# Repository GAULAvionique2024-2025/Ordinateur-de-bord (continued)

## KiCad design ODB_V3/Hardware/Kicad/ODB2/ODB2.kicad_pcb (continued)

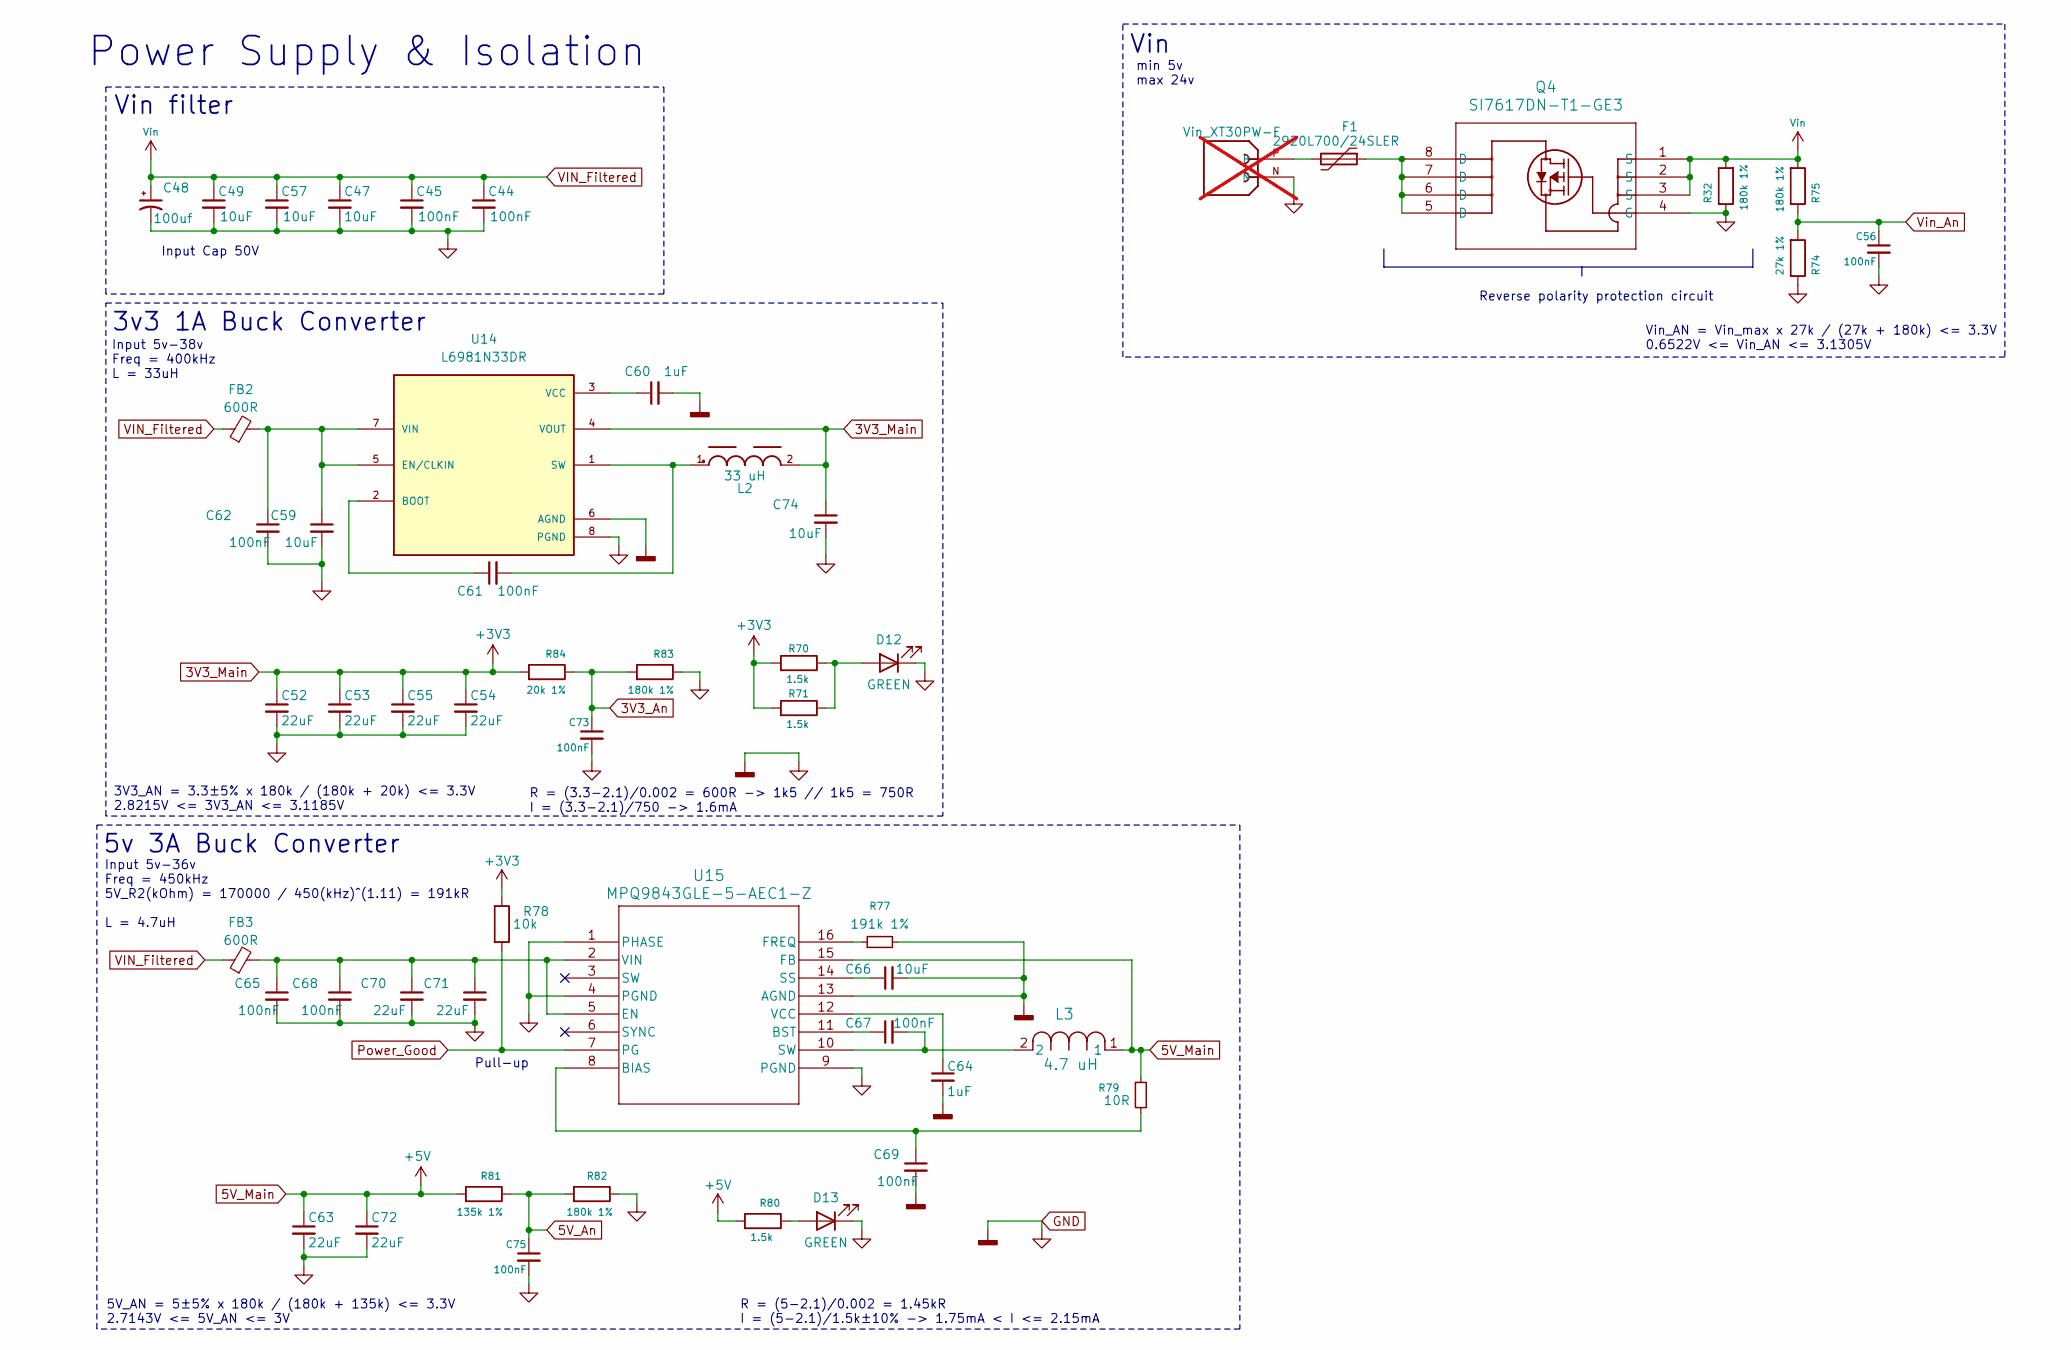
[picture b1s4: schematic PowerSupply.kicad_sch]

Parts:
C44, C45, C56, C61, C62, C65, C67, C68, C69, C73, C75: 100nF; C_0402_1005Metric; Manufacturer_Part_Number CC0402KRX5R9BB104; DigiKey_Part_Number 311-3342-1-ND
C47, C49, C57, C59, C66, C74: 10uF; C_0603_1608Metric; Manufacturer_Part_Number GMC10X5R106M35NT; DigiKey_Part_Number 4713-GMC10X5R106M35NTTR-ND
C48: 100uf; WCAP-PSHP_8X8.7_DXL_; Manufacturer_Part_Number 875115652007; DigiKey_Part_Number 732-11942-1-ND
C52, C53, C54, C55, C63, C70, C71, C72: 22uF; C_0805_2012Metric; Manufacturer_Part_Number TMK212BBJ226MG-TT; DigiKey_Part_Number 587-6359-1-ND
C60, C64: 1uF; C_0603_1608Metric; Manufacturer_Part_Number C0603C105K4RACTU; DigiKey_Part_Number 399-C0603C105K4RACTUCT-ND
D12, D13: GREEN; LED_QBLP601-AG15; Manufacturer_Part_Number QBLP601-AG15; DigiKey_Part_Number 1516-QBLP601-AG15CT-ND
F1: 2920L700/24SLER; Fuse_2920_7451Metric; Manufacturer_Part_Number 2920L700/24SLER; DigiKey_Part_Number 18-2920L700/24SLERCT-ND
FB2, FB3: 600R; L_1210_3225Metric; Manufacturer_Part_Number FBMH3225HM601NT; DigiKey_Part_Number 587-1755-1-ND
J8: Vin_XT30PW-F; AMASS_XT30PW-F; PARTREV 1.2; not fitted
L2: 33 uH; WE-PD_1245; Manufacturer_Part_Number 7447715330; Digikey 732-2196-1-ND
L3: 4.7 uH; IND_PA4342_PUL; Manufacturer_Part_Number PA4342.472NLT; Digikey 553-3001-1-ND
Q4: SI7617DN-T1-GE3; POWERPAK_1212-8_VIS; Manufacturer_Part_Number SI7617DN-T1-GE3; DigiKey_Part_Number SI7617DN-T1-GE3CT-ND
R32, R75, R82, R83: 180k 1%; R_0603_1608Metric; Manufacturer_Part_Number ERA-3AEB184V; DigiKey_Part_Number P180KDBCT-ND
R70, R71, R80: 1.5k; R_0603_1608Metric; Manufacturer_Part_Number ERA-3AEB152V; DigiKey_Part_Number P1.5KDBCT-ND
R74: 27k 1%; R_0603_1608Metric; Manufacturer_Part_Number RG1608P-273-B-T5; DigiKey_Part_Number RG16P27.0KBCT-ND
R77: 191k 1%; R_0603_1608Metric; Manufacturer_Part_Number RT0603BRD07191KL; DigiKey_Part_Number YAG1553CT-ND
R78: 10k; R_0603_1608Metric; Manufacturer_Part_Number RC0603FR-0710KL; DigiKey_Part_Number 311-10.0KHRCT-ND
R79: 10R; R_0402_1005Metric; Manufacturer_Part_Number CRCW040210R0FKED; DigiKey_Part_Number 541-10.0LCT-ND
R81: 135k 1%; R_0603_1608Metric; Manufacturer_Part_Number RT0603BRD07135KL; DigiKey_Part_Number 13-RT0603BRD07135KLCT-ND
R84: 20k 1%; R_0603_1608Metric; Manufacturer_Part_Number ERA-3AEB203V; DigiKey_Part_Number P20KDBCT-ND
U14: L6981N33DR; SOIC127P600X175-8N; PARTREV 3; DigiKey_Part_Number 497-L6981N33DRCT-ND
U15: MPQ9843GLE-5-AEC1-Z; QFN-16_ MPQ9843; Manufacturer_Part_Number MPQ9843GLE-5-AEC1-Z; DigiKey_Part_Number 1589-MPQ9843GLE-5-AEC1-ZCT-ND

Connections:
3V3_An: C73.1, R83.2, R84.1; also elsewhere on the board
3V3_Main: C52.1, C53.1, C54.1, C55.1, C74.1, L2.2, R70.2, R71.2, R78.1, R84.2, U14.4 (VOUT); also elsewhere on the board
5V_An: C75.1, R81.1, R82.2; also elsewhere on the board
5V_Main: C63.1, C72.1, L3.1, R79.1, R80.2, R81.2, U15.15 (FB); also elsewhere on the board
GND: C44.2, C45.2, C47.2, C48.2, C49.2, C52.2, C53.2, C54.2, C55.2, C56.2, C57.2, C59.2, C60.2, C62.2, C63.2, C64.2, C65.2, C66.2, C68.2, C69.2, C70.2, C71.2, C72.2, C73.2, C74.2, C75.2, D12.1 (K), D13.1 (K), J8.N, Q4.4 (G), R32.1, R74.1, R77.2, R82.1, R83.1, U14.6 (AGND), U14.8 (PGND), U15.1 (PHASE), U15.4 (PGND), U15.9 (PGND), U15.13 (AGND); also elsewhere on the board
unnamed: C67.2, L3.2, U15.10 (SW)
unnamed: D12.2 (A), R70.1, R71.1
unnamed: D13.2 (A), R80.1
unnamed: F1.1, Q4.5 (D), Q4.6 (D), Q4.7 (D), Q4.8 (D), Q4.9 (D)
unnamed: F1.2, J8.P
unnamed: C61.1, U14.2 (BOOT)
unnamed: C59.1, C62.1, FB2.2, U14.5 (EN/CLKIN), U14.7 (VIN)
unnamed: C61.2, L2.1, U14.1 (SW)
unnamed: C60.1, U14.3 (VCC)
unnamed: C69.1, R79.2, U15.8 (BIAS)
unnamed: C67.1, U15.11 (BST)
unnamed: C65.1, C68.1, C70.1, C71.1, FB3.2, U15.2 (VIN), U15.5 (EN)
unnamed: R77.1, U15.16 (FREQ)
unnamed: C66.1, U15.14 (SS)
unnamed: C64.1, U15.12 (VCC)
Power_Good: R78.2, U15.7 (PG); also elsewhere on the board
VIN_Filtered: C44.1, C45.1, C47.1, C48.1, C49.1, C57.1, FB2.1, FB3.1, Q4.1 (S), Q4.2 (S), Q4.3 (S), R32.2, R75.2; also elsewhere on the board
Vin_An: C56.1, R74.2, R75.1; also elsewhere on the board

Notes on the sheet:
Input 5v-38v Freq = 400kHz L = 33uH
Input Cap 50V
Vin_AN = Vin_max x 27k / (27k + 180k) <= 3.3V 0.6522V <= Vin_AN <= 3.1305V
3v3 1A Buck Converter
5V_AN = 5±5% x 180k / (180k + 135k) <= 3.3V 2.7143V <= 5V_AN <= 3V
Vin
Pull-up
R = (3.3-2.1)/0.002 = 600R -> 1k5 // 1k5 = 750R I = (3.3-2.1)/750 -> 1.6mA
Reverse polarity protection circuit
3V3_AN = 3.3±5% x 180k / (180k + 20k) <= 3.3V 2.8215V <= 3V3_AN <= 3.1185V
Vin filter
Input 5v-36v Freq = 450kHz 5V_R2(kOhm) = 170000 / 450(kHz)^(1.11) = 191kR L = 4.7uH
R = (5-2.1)/0.002 = 1.45kR I = (5-2.1)/1.5k±10% -> 1.75mA < I <= 2.15mA
min 5v max 24v
Power Supply & Isolation
5v 3A Buck Converter

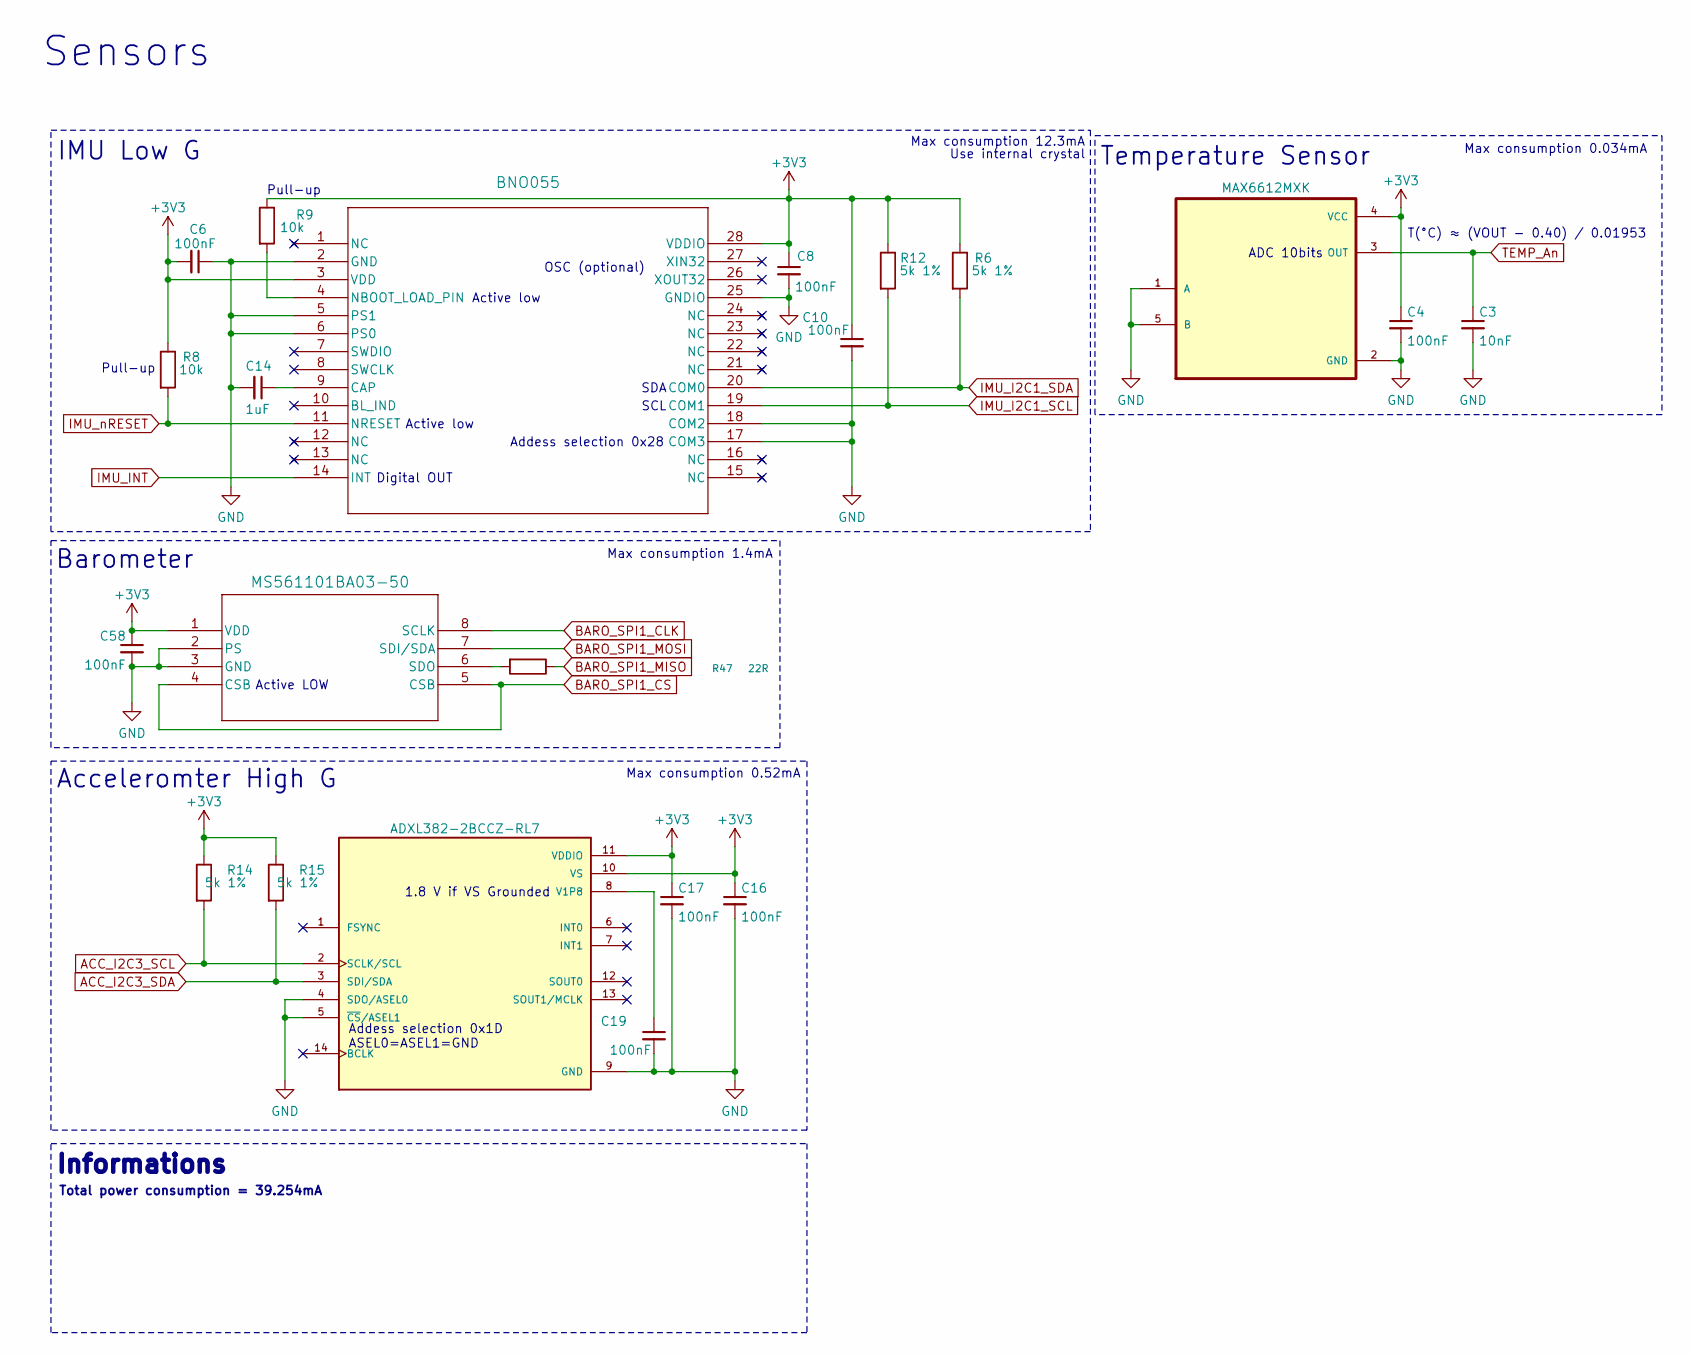
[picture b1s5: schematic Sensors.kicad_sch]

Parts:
C3: 10nF; C_0402_1005Metric; Manufacturer_Part_Number GRM155R71C103KA01D; DigiKey_Part_Number 490-1313-1-ND
C4, C6, C8, C10, C16, C17, C19, C58: 100nF; C_0402_1005Metric; Manufacturer_Part_Number CC0402KRX5R9BB104; DigiKey_Part_Number 311-3342-1-ND
C14: 1uF; C_0603_1608Metric; Manufacturer_Part_Number C0603C105K4RACTU; DigiKey_Part_Number 399-C0603C105K4RACTUCT-ND
R6, R12, R14, R15: 5k 1%; R_0603_1608Metric; Manufacturer_Part_Number MCT06030D5001BP500; DigiKey_Part_Number 541-MCT06030D5001BP500CT-ND
R8, R9: 10k; R_0603_1608Metric; Manufacturer_Part_Number RC0603FR-0710KL; DigiKey_Part_Number 311-10.0KHRCT-ND
R47: 22R; R_0402_1005Metric; Manufacturer_Part_Number AC0402FR-0722RL; DigiKey_Part_Number YAG3460CT-ND
U3: MAX6612MXK; SOT65P210X110-5N; Manufacturer_Part_Number MAX6612MXK+T; DigiKey_Part_Number MAX6612MXK+TCT-ND
U4: BNO055; QFN_BNO055_BOS; Manufacturer_Part_Number BNO055; DigiKey_Part_Number 828-1058-1-ND
U5: ADXL382-2BCCZ-RL7; XDCR_ADXL382-2BCCZ-RL7; PARTREV 0; DigiKey_Part_Number 505-ADXL382-2BCCZ-RL7CT-ND
U13: MS561101BA03-50; SON8_MS5611_TEC; Manufacturer_Part_Number MS561101BA03-50; DigiKey_Part_Number 223-1622-1-ND

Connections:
3V3_Main: C4.1, C6.2, C8.1, C10.1, C16.1, C17.1, C58.1, R6.1, R8.1, R9.1, R12.1, R14.1, R15.1, U3.4 (VCC), U4.3 (VDD), U4.28 (VDDIO), U5.10 (VS), U5.11 (VDDIO), U13.1 (VDD); also elsewhere on the board
ACC_I2C3_SCL: R14.2, U5.2 (SCLK/SCL); also elsewhere on the board
ACC_I2C3_SDA: R15.2, U5.3 (SDI/SDA); also elsewhere on the board
BARO_SPI1_CLK: U13.8 (SCLK); also elsewhere on the board
BARO_SPI1_CS: U13.4 (CSB), U13.5 (CSB); also elsewhere on the board
BARO_SPI1_MISO: R47.1; also elsewhere on the board
BARO_SPI1_MOSI: U13.7 (SDI/SDA); also elsewhere on the board
GND: C3.2, C4.2, C6.1, C8.2, C10.2, C14.2, C16.2, C17.2, C19.2, C58.2, U3.1 (A), U3.2 (GND), U3.5 (B), U4.2 (GND), U4.5 (PS1), U4.6 (PS0), U4.17 (COM3), U4.18 (COM2), U4.25 (GNDIO), U5.4 (SDO/ASEL0), U5.5 (~CS/ASEL1), U5.9 (GND), U13.2 (PS), U13.3 (GND); also elsewhere on the board
IMU_I2C1_SCL: R12.2, U4.19 (COM1); also elsewhere on the board
IMU_I2C1_SDA: R6.2, U4.20 (COM0); also elsewhere on the board
IMU_INT: U4.14 (INT); also elsewhere on the board
IMU_nRESET: R8.2, U4.11 (NRESET); also elsewhere on the board
unnamed: C14.1, U4.9 (CAP)
unnamed: R9.2, U4.4 (NBOOT_LOAD_PIN)
unnamed: C19.1, U5.8 (V1P8)
unnamed: R47.2, U13.6 (SDO)
TEMP_An: C3.1, U3.3 (OUT); also elsewhere on the board

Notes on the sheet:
OSC (optional)
Max consumption 0.52mA
Active low
Max consumption 12.3mA
Total power consumption = 39.254mA
Pull-up
SCL
Temperature Sensor
T(°C) ≈ (VOUT - 0.40) / 0.01953
Addess selection 0x1D ASEL0=ASEL1=GND
Informations
1.8 V if VS Grounded
Max consumption 0.034mA
Sensors
Max consumption 1.4mA
Acceleromter High G
Digital OUT
Barometer
Addess selection 0x28
Use internal crystal
Active LOW
SDA
ADC 10bits
IMU Low G

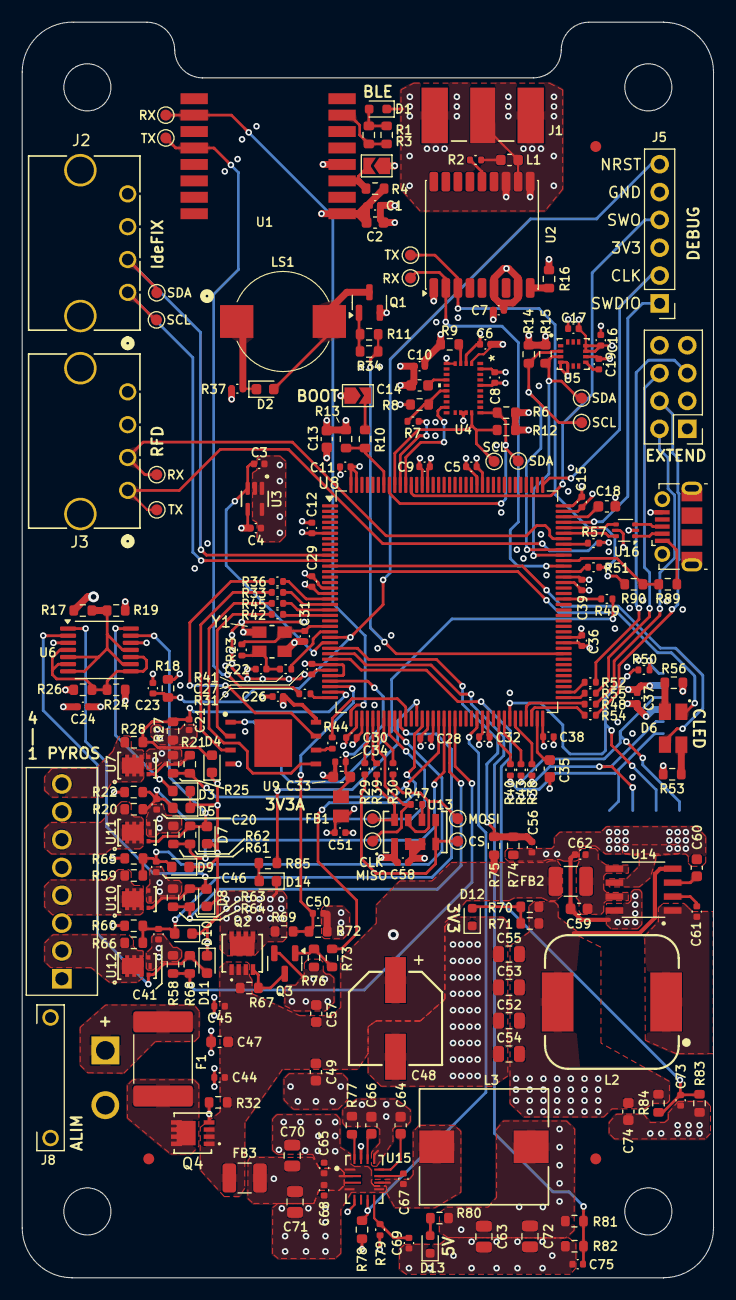
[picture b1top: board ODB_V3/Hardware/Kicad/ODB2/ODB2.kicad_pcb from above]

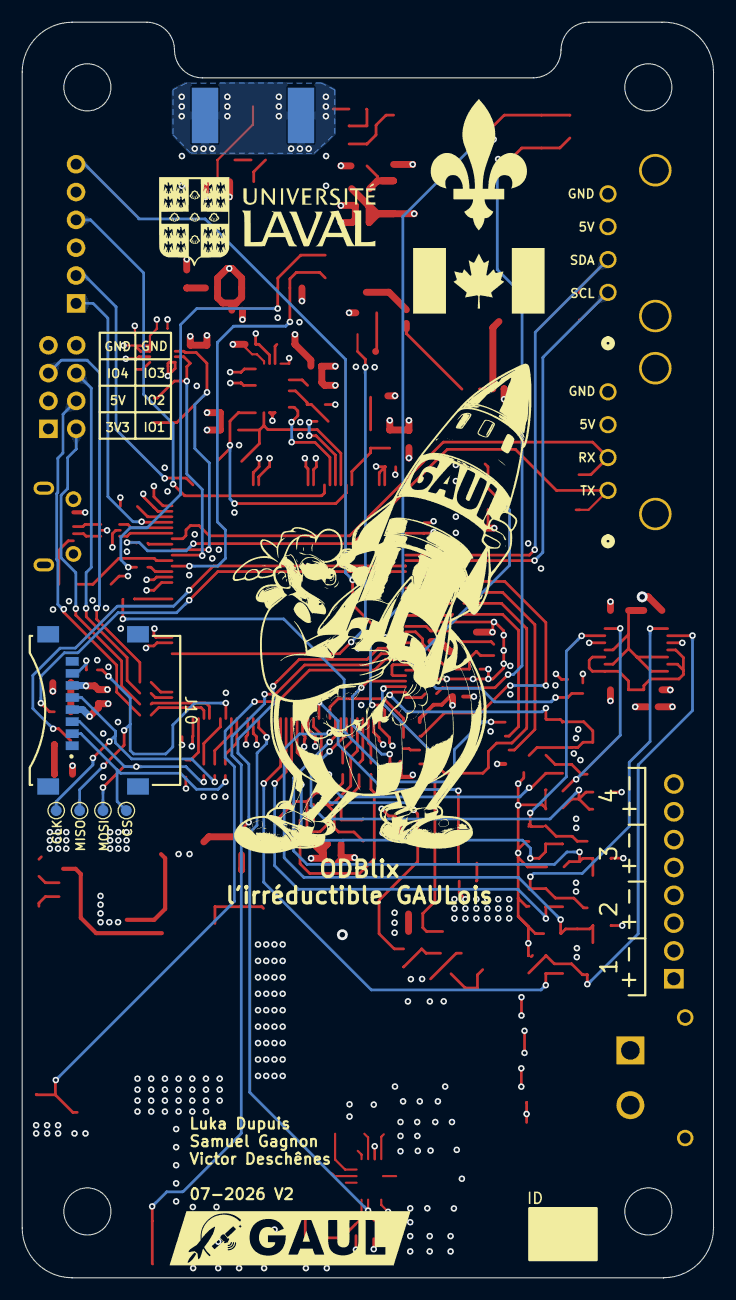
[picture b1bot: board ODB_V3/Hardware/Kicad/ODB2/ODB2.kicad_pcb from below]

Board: 6 copper layers, 63.1 x 114.6 mm, 233 parts (5 on the bottom side), 139 nets.

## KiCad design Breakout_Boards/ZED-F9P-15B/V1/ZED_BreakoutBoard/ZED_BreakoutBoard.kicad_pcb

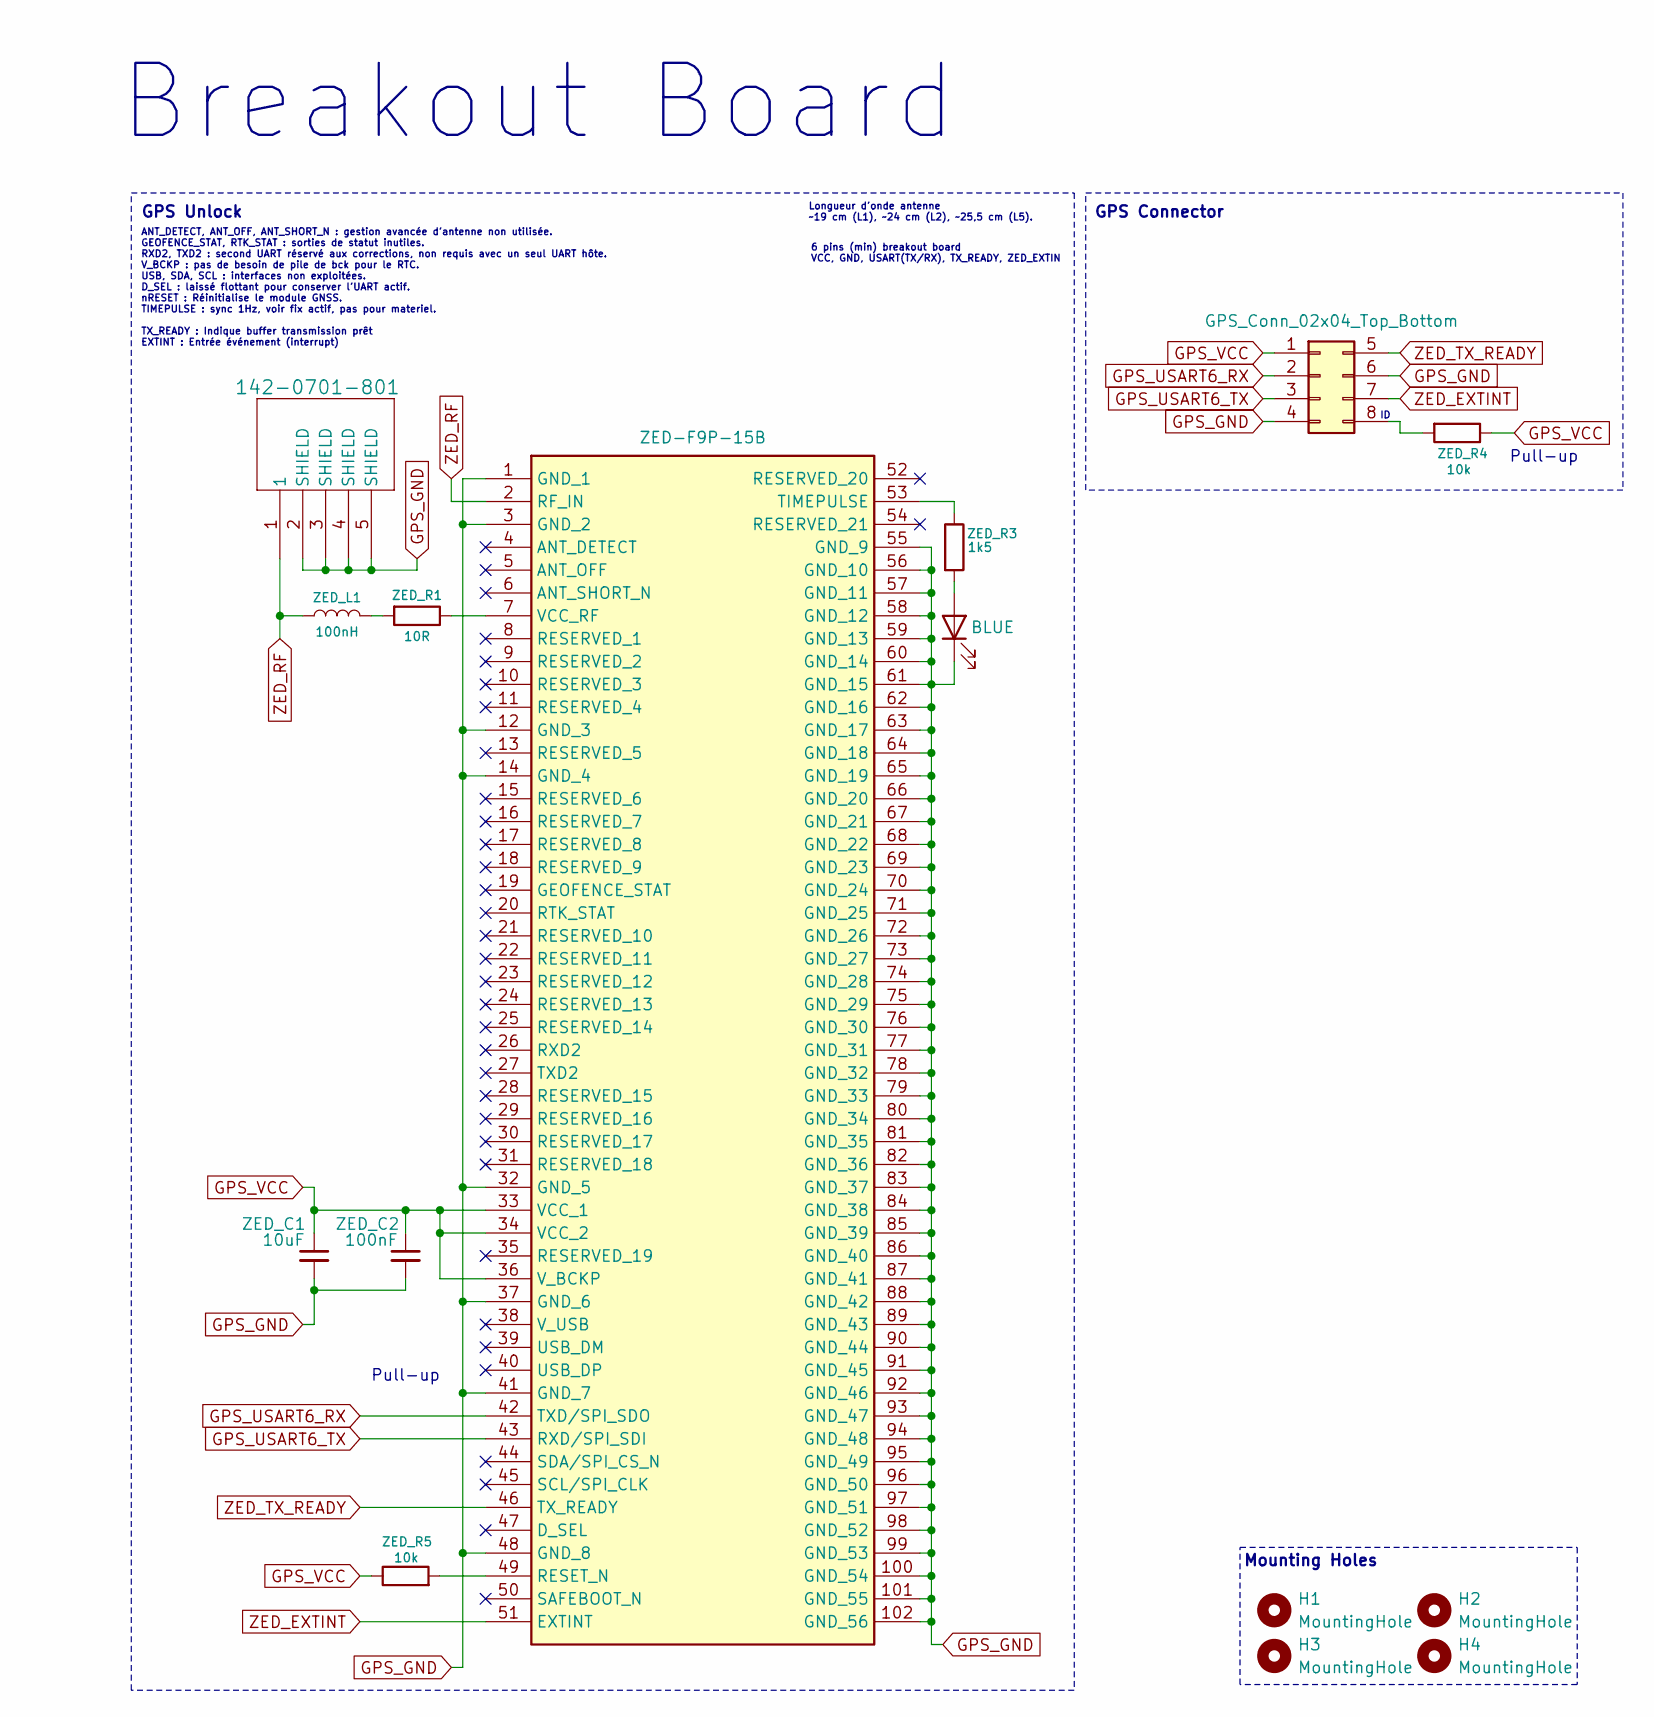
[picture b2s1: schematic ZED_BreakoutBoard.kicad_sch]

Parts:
H1, H2, H3, H4: MountingHole; MountingHole_2.2mm_M2
IC1: ZED-F9P-15B; ZEDF9P15B; Mouser Part Number 377-ZED-F9P-15B
J1: 142-0701-801; CONN_142-0701-801
J2: GPS_Conn_02x04_Top_Bottom; PinHeader_2x04_P2.54mm_Vertical
ZED_C1: 10uF; C_0603_1608Metric
ZED_C2: 100nF; C_0603_1608Metric
ZED_L1: 100nH; L_0603_1608Metric
ZED_LED1: BLUE; LED_0603_1608Metric
ZED_R1: 10R; R_0603_1608Metric
ZED_R3: 1k5; R_0603_1608Metric
ZED_R4, ZED_R5: 10k; R_0603_1608Metric

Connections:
GPS_GND: IC1.1 (GND_1), IC1.3 (GND_2), IC1.12 (GND_3), IC1.14 (GND_4), IC1.32 (GND_5), IC1.37 (GND_6), IC1.41 (GND_7), IC1.48 (GND_8), IC1.55 (GND_9), IC1.56 (GND_10), IC1.57 (GND_11), IC1.58 (GND_12), IC1.59 (GND_13), IC1.60 (GND_14), IC1.61 (GND_15), IC1.62 (GND_16), IC1.63 (GND_17), IC1.64 (GND_18), IC1.65 (GND_19), IC1.66 (GND_20), IC1.67 (GND_21), IC1.68 (GND_22), IC1.69 (GND_23), IC1.70 (GND_24), IC1.71 (GND_25), IC1.72 (GND_26), IC1.73 (GND_27), IC1.74 (GND_28), IC1.75 (GND_29), IC1.76 (GND_30), IC1.77 (GND_31), IC1.78 (GND_32), IC1.79 (GND_33), IC1.80 (GND_34), IC1.81 (GND_35), IC1.82 (GND_36), IC1.83 (GND_37), IC1.84 (GND_38), IC1.85 (GND_39), IC1.86 (GND_40), IC1.87 (GND_41), IC1.88 (GND_42), IC1.89 (GND_43), IC1.90 (GND_44), IC1.91 (GND_45), IC1.92 (GND_46), IC1.93 (GND_47), IC1.94 (GND_48), IC1.95 (GND_49), IC1.96 (GND_50), IC1.97 (GND_51), IC1.98 (GND_52), IC1.99 (GND_53), IC1.100 (GND_54), IC1.101 (GND_55), IC1.102 (GND_56), J1.2 (SHIELD), J1.3 (SHIELD), J1.4 (SHIELD), J1.5 (SHIELD), J2.4, J2.6, ZED_C1.2, ZED_C2.2, ZED_LED1.1 (K)
GPS_USART6_RX: IC1.42 (TXD/SPI_SDO), J2.2
GPS_USART6_TX: IC1.43 (RXD/SPI_SDI), J2.3
GPS_VCC: IC1.33 (VCC_1), IC1.34 (VCC_2), IC1.36 (V_BCKP), J2.1, ZED_C1.1, ZED_C2.1, ZED_R4.1, ZED_R5.1
unnamed: IC1.49 (RESET_N), ZED_R5.2
unnamed: IC1.53 (TIMEPULSE), ZED_R3.1
unnamed: IC1.7 (VCC_RF), ZED_R1.1
unnamed: J2.8, ZED_R4.2
unnamed: ZED_L1.2, ZED_R1.2
unnamed: ZED_LED1.2 (A), ZED_R3.2
ZED_EXTINT: IC1.51 (EXTINT), J2.7
ZED_RF: IC1.2 (RF_IN), J1.1, ZED_L1.1
ZED_TX_READY: IC1.46 (TX_READY), J2.5

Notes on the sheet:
Mounting Holes
GPS Connector
Pull-up
GPS Unlock
Breakout Board
6 pins (min) breakout board VCC, GND, USART(TX/RX), TX_READY, ZED_EXTIN
ANT_DETECT, ANT_OFF, ANT_SHORT_N : gestion avancée d'antenne non utilisée. GEOFENCE_STAT, RTK_STAT : sorties de statut inutiles. RXD2, TXD2 : second UART réservé aux corrections, non requis avec un seul UART hôte. V_BCKP : pas de besoin de pile de bck pour le RTC. USB, SDA, SCL : interfaces non exp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
Longueur d'onde antenne ~19 cm (L1), ~24 cm (L2), ~25,5 cm (L5).

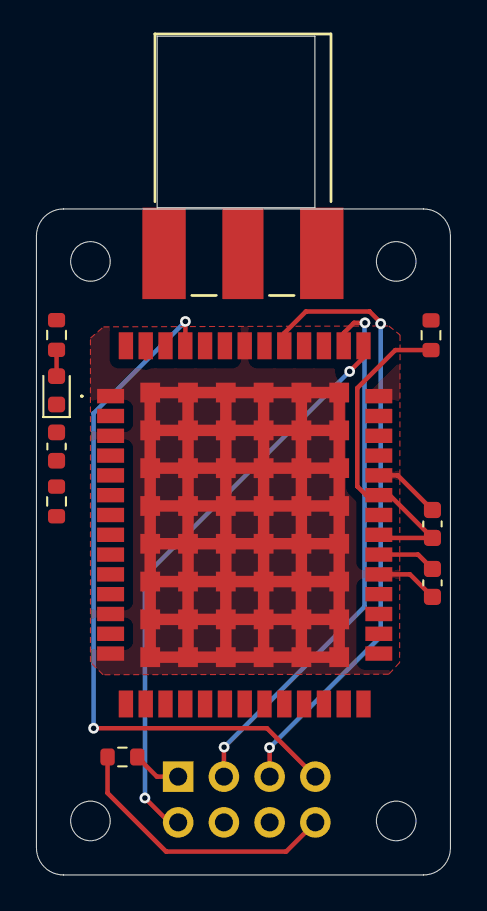
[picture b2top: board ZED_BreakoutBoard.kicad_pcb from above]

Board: 2 copper layers, 23.0 x 37.0 mm, 15 parts (1 on the bottom side), 13 nets.

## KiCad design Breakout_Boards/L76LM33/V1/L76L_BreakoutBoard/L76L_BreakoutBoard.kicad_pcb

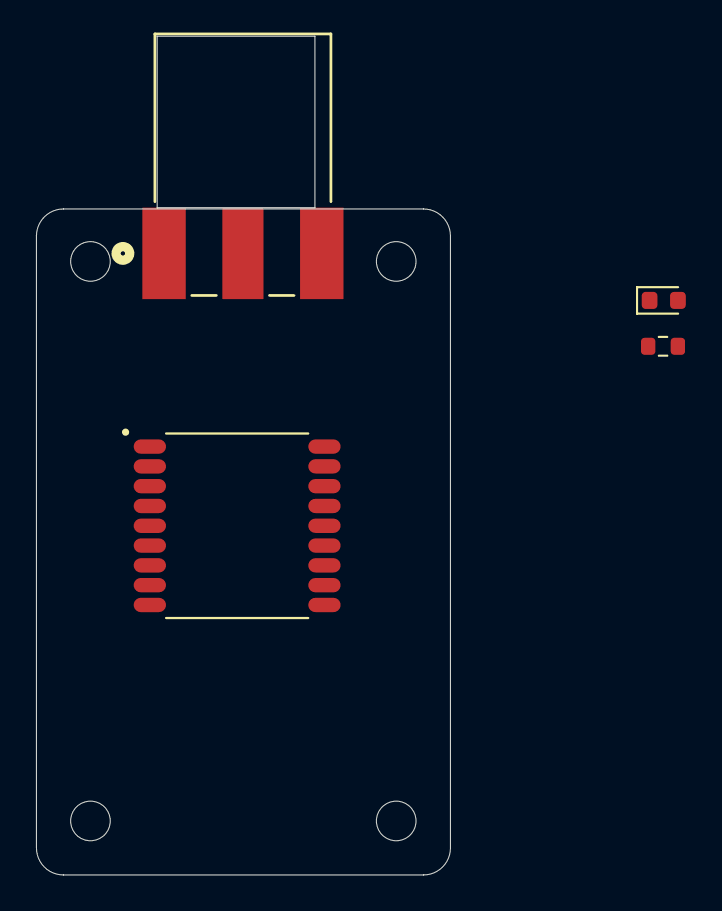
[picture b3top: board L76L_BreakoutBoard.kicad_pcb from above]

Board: 2 copper layers, 23.0 x 46.6 mm, 8 parts (0 on the bottom side), 4 nets, no tracks yet.

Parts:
H1, H2, H3, H4: MountingHole; MountingHole_2.2mm_M2
J1: 142-0701-801; CONN_142-0701-801
L76LM33_R3: 1k5; R_0603_1608Metric
U1: L76L-M33; XCVR_L76L-M33
ZED_LED1: BLUE; LED_0603_1608Metric

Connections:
GPS_GND: J1.2 (SHIELD), J1.3 (SHIELD), J1.4 (SHIELD), J1.5 (SHIELD), U1.1 (GND), U1.9 (RESET), U1.10 (GND__1), U1.12 (GND__2), ZED_LED1.1 (K)
GPS_VCC: L76LM33_R3.1, U1.6 (V_BCKP), U1.8 (VCC)
L76LM33_RF: J1.1, U1.11 (RF_IN)
unnamed: L76LM33_R3.2, ZED_LED1.2 (A)
